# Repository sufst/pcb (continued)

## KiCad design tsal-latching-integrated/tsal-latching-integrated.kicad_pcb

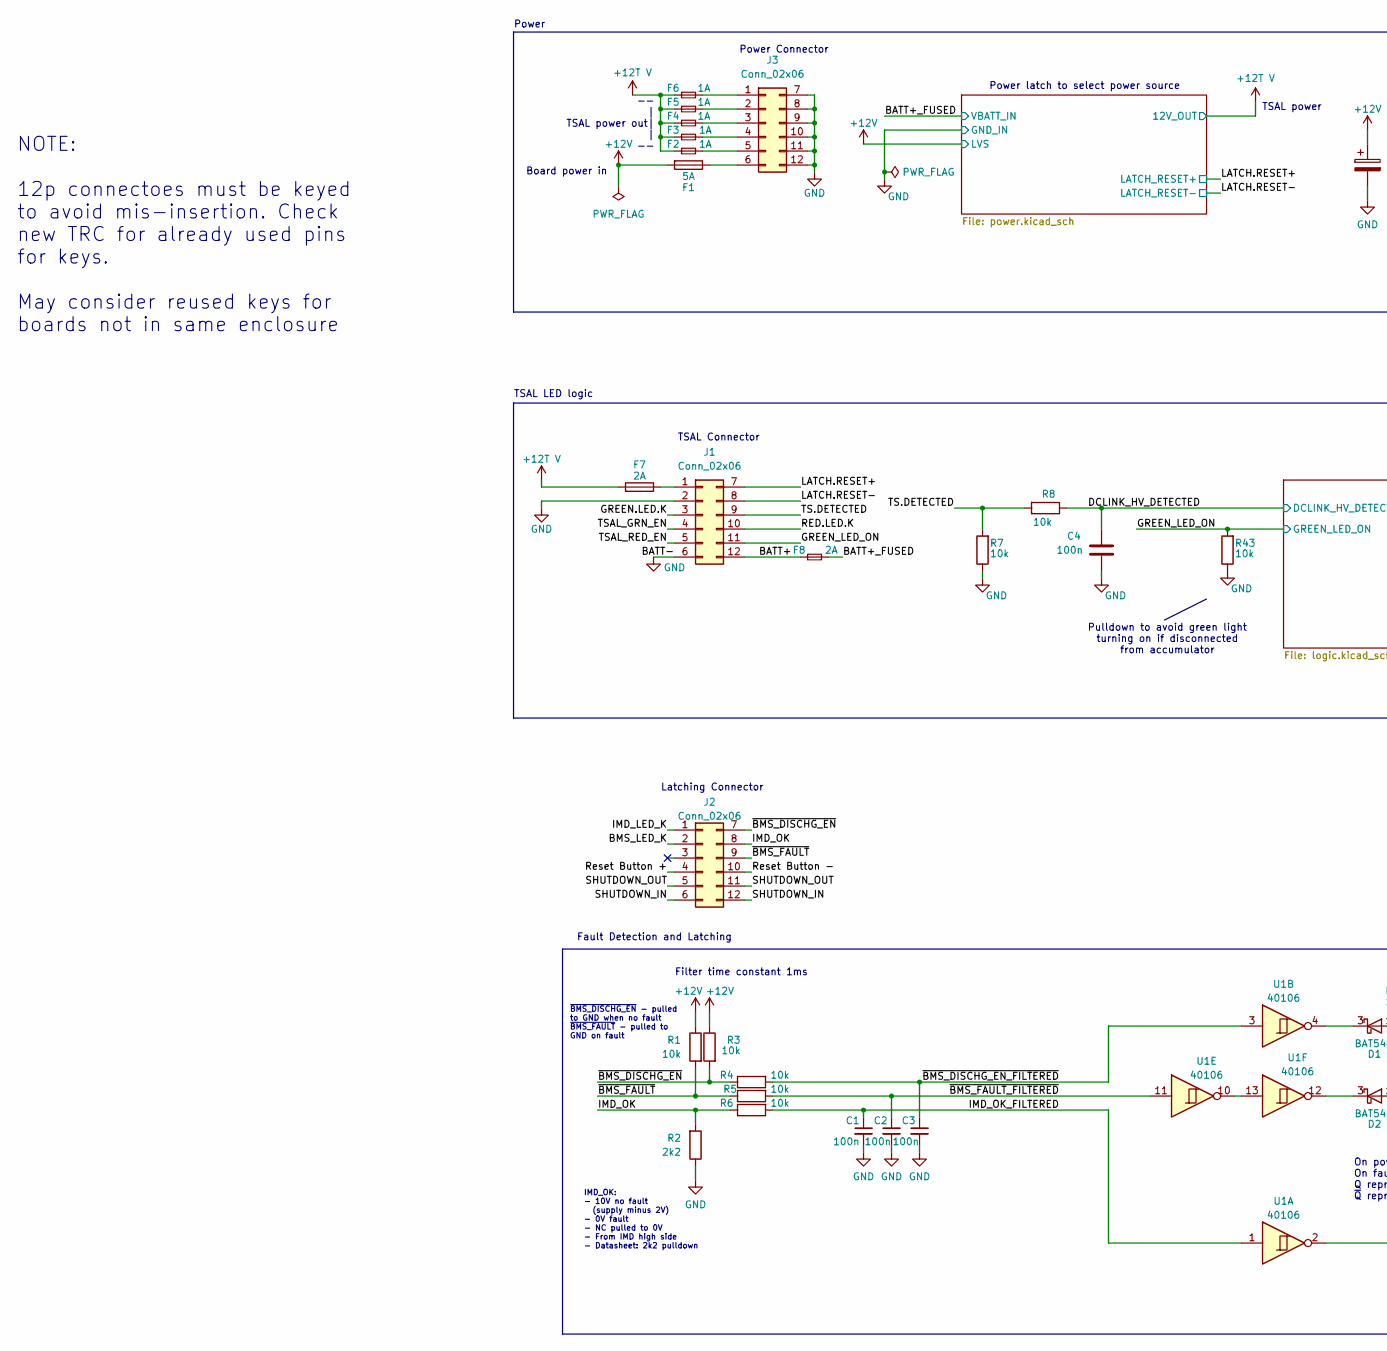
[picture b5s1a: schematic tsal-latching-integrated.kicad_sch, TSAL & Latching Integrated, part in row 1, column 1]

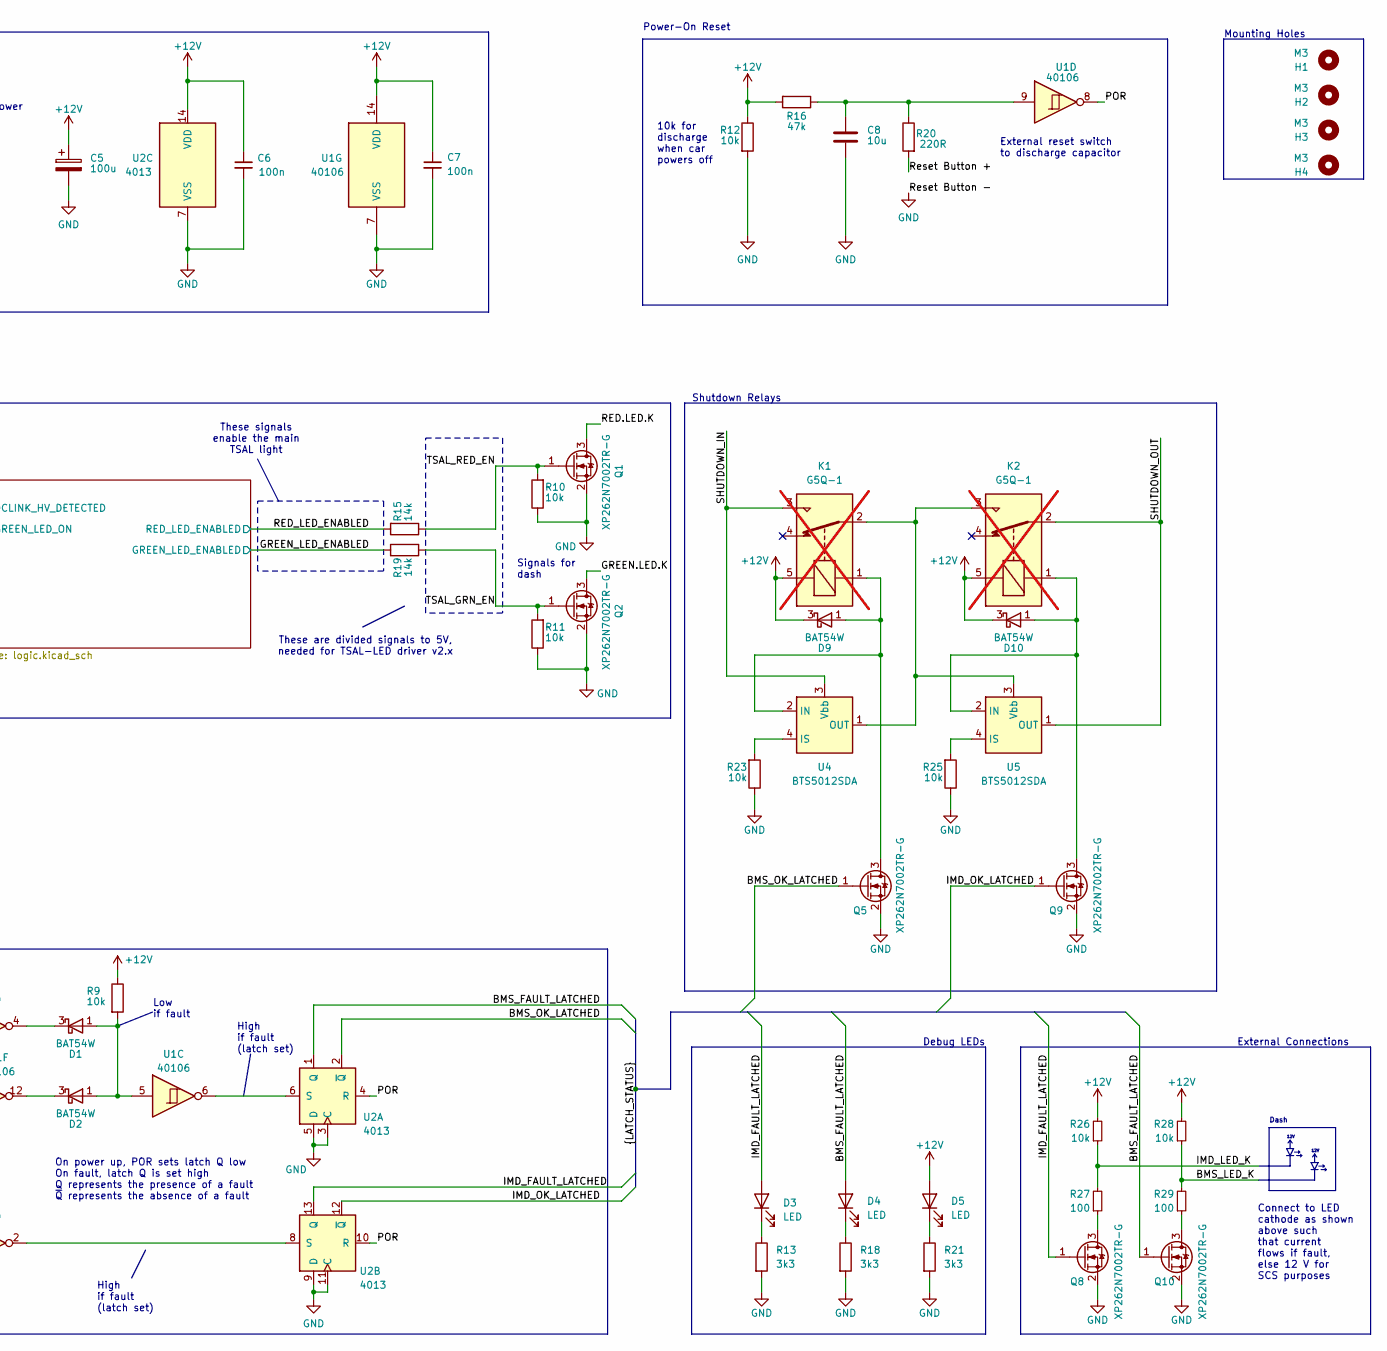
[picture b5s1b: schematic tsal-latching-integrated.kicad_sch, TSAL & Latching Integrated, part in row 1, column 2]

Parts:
C1, C2, C3, C4, C6, C7: 100n; C_0603_1608Metric; Mouser PN 187-CL10B104KB85PNL
C5: 100u; CP_Radial_D5.0mm_P2.00mm; Mouser PN 710-860010572002
C8: 10u; C_0805_2012Metric; Mouser PN 81-GRM21BR61E106KA3K
D1, D2, D9, D10: BAT54W; SOT-323_SC-70
D3, D4, D5: LED; LED_0603_1608Metric
F1: 5A; Fuse_0603_1608Metric_Pad1.05x0.95mm_HandSolder; Mouser PN 603-JB06F5001R
F2, F3, F4, F5, F6: 1A; Fuse_0603_1608Metric_Pad1.05x0.95mm_HandSolder; Mouser PN 791-FCC16102ADTP
F7, F8: 2A; Fuse_0603_1608Metric_Pad1.05x0.95mm_HandSolder; Mouser PN 791-FCC16202ADTP
H1, H2, H3, H4: M3; MountingHole_3.2mm_M3
J1, J2, J3: Conn_02x06; Molex_Micro-Fit_3.0_43045-1200_2x06_P3.00mm_Horizontal
K1, K2: G5Q-1; Relay_SPDT_Omron-G5Q-1; Mouser PN 653-G5Q-1A-EUDC12; not fitted
Q1, Q2, Q5, Q8, Q9, Q10: XP262N7002TR-G; SOT-23; Mouser PN 865-XP262N7002TR-G
R1, R3, R4, R5, R6, R7, R8, R9, R10, R11, R12, R23, R25, R26, R28, R43: 10k; R_0603_1608Metric; Mouser PN 603-RT0603FRE1310KL
R2: 2k2; R_0603_1608Metric; Mouser PN 603-RT0603FRE072K2L
R13, R18, R21: 3k3; R_0603_1608Metric; Mouser PN 594-MCT06030C3301FP5
R15, R19: 14k; R_0603_1608Metric; Mouser PN 603-RT0603FRE0714KL
R16: 47k; R_0603_1608Metric; Mouser PN 603-RT0603FRE1347KL
R20: 220R; R_0603_1608Metric; Mouser PN 603-RT0603FRE07220RL
R27, R29: 100; R_0603_1608Metric; Mouser PN 603-RT0603FRE07100RL
U1: 40106; SOIC-14_3.9x8.7mm_P1.27mm; Mouser PN 595-CD40106BM
U2: 4013; SOIC-14_3.9x8.7mm_P1.27mm
U4, U5: BTS5012SDA; TO-252-4; Mouser PN 726-BTS5012SDA

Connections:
+12T V: F2.1, F3.1, F4.1, F5.1, F6.1, F7.2; also elsewhere on the board
+12V: C5.1, C6.1, C7.1, D5.2 (A), D9.3 (K), D10.3 (K), F1.2, K1.5, K2.5, R1.1, R3.1, R9.1, R12.1, R16.2, R26.2, R28.2, U1.14 (VDD), U2.14 (VDD); also elsewhere on the board
/BATT+: F8.1, J1.12
/BATT+_FUSED: F8.2; also elsewhere on the board
/BMS_FAULT_LATCHED: D4.2 (A), Q10.1 (G), U2.1 (Q)
/BMS_LED_K: J2.2, R28.1, R29.2
/BMS_OK_LATCHED: Q5.1 (G), U2.2 (~Q)
/DCLINK_HV_DETECTED: C4.1, R8.1; also elsewhere on the board
/GREEN.LED.K: J1.3, Q2.3 (D)
/GREEN_LED_ENABLED: R19.2; also elsewhere on the board
/GREEN_LED_ON: J1.11, R43.2; also elsewhere on the board
/IMD_FAULT_LATCHED: D3.2 (A), Q8.1 (G), U2.13 (Q)
/IMD_LED_K: J2.1, R26.1, R27.2
/IMD_OK: J2.8, R2.2, R6.1
/IMD_OK_FILTERED: C1.1, R6.2, U1.1
/IMD_OK_LATCHED: Q9.1 (G), U2.12 (~Q)
/LATCH.RESET+: J1.7; also elsewhere on the board
/LATCH.RESET-: J1.8; also elsewhere on the board
/POR: U1.8, U2.4 (R), U2.10 (R)
/RED.LED.K: J1.10, Q1.3 (D)
/RED_LED_ENABLED: R15.2; also elsewhere on the board
/Reset Button +: J2.4, R20.2
/SHUTDOWN_IN: J2.6, J2.12, K1.3, U4.3 (Vbb)
/SHUTDOWN_OUT: J2.5, J2.11, K2.2, U5.1 (OUT), U5.5 (OUT)
/TS.DETECTED: J1.9, R7.2, R8.2
/TSAL_GRN_EN: J1.4, Q2.1 (G), R11.2, R19.1
/TSAL_RED_EN: J1.5, Q1.1 (G), R10.2, R15.1
/~BMS_DISCHG_EN_FILTERED: C3.1, R4.2, U1.3
/~BMS_DISCHG_EN: J2.7, R3.2, R4.1
/~BMS_FAULT_FILTERED: C2.1, R5.2, U1.11
/~BMS_FAULT: J2.9, R1.2, R5.1
GND: C1.2, C2.2, C3.2, C4.2, C5.2, C6.2, C7.2, C8.2, J1.2, J1.6, J2.10, J3.7, J3.8, J3.9, J3.10, J3.11, J3.12, Q1.2 (S), Q2.2 (S), Q5.2 (S), Q8.2 (S), Q9.2 (S), Q10.2 (S), R2.1, R7.1, R10.1, R11.1, R12.2, R13.2, R18.2, R21.2, R23.1, R25.1, R43.1, U1.7 (VSS), U2.3 (C), U2.5 (D), U2.7 (VSS), U2.9 (D), U2.11 (C); also elsewhere on the board
unnamed: C8.1, R16.1, R20.1, U1.9
unnamed: D1.1 (A), D2.1 (A), R9.2, U1.5
unnamed: D1.3 (K), U1.4
unnamed: D2.3 (K), U1.12
unnamed: D3.1 (K), R13.1
unnamed: D4.1 (K), R18.1
unnamed: D5.1 (K), R21.1
unnamed: D9.1 (A), K1.1, Q5.3 (D), U4.2 (IN)
unnamed: D10.1 (A), K2.1, Q9.3 (D), U5.2 (IN)
unnamed: F7.1, J1.1
unnamed: F6.2, J3.1
unnamed: F5.2, J3.2
unnamed: F4.2, J3.3
unnamed: F3.2, J3.4
unnamed: F2.2, J3.5
unnamed: F1.1, J3.6
unnamed: Q8.3 (D), R27.1
unnamed: Q10.3 (D), R29.1
unnamed: U1.10, U1.13
unnamed: U1.6, U2.6 (S)
unnamed: U1.2, U2.8 (S)
unnamed: R23.2, U4.4 (IS)
unnamed: R25.2, U5.4 (IS)
unnamed: K1.2, K2.3, U4.1 (OUT), U4.5 (OUT), U5.3 (Vbb)

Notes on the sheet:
Power-On Reset
These are divided signals to 5V, needed for TSAL-LED driver v2.x
IMD_OK: - 10V no fault (supply minus 2V) - 0V fault - NC pulled to 0V - From IMD high side - Datasheet: 2k2 pulldown
Low if fault
Board power in
TSAL Connector
High if fault (latch set)
Filter time constant 1ms
Debug LEDs
Dash
TSAL LED logic
TSAL power
12V
NOTE: 12p connectoes must be keyed to avoid mis-insertion. Check new TRC for already used pins for keys. May consider reused keys for boards not in same enclosure
Latching Connector
Shutdown Relays
Signals for dash
Power latch to select power source
-- | TSAL power out| | --
Connect to LED cathode as shown above such that current flows if fault, else 12 V for SCS purposes
Pulldown to avoid green light turning on if disconnected from accumulator
External reset switch to discharge capacitor
Power
These signals enable the main TSAL light
10k for discharge when car powers off
~{BMS_DISCHG_EN} - pulled to GND when no fault ~{BMS_FAULT} - pulled to GND on fault
High if fault (latch set)
On power up, POR sets latch Q low On fault, latch Q is set high Q represents the presence of a fault ~{Q} represents the absence of a fault
Fault Detection and Latching
External Connections
Power Connector
Mounting Holes

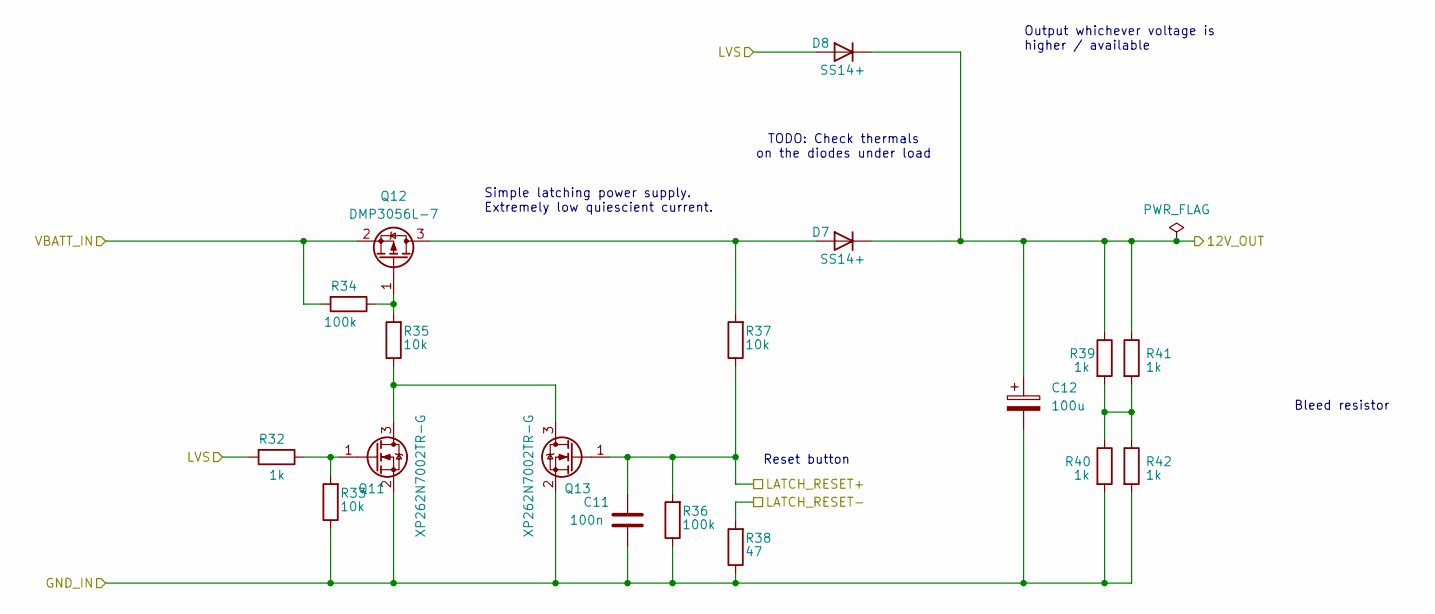
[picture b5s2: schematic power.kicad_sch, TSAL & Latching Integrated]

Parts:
C11: 100n; C_0603_1608Metric; Mouser PN 187-CL10B104KB85PNL
C12: 100u; CP_Radial_D6.3mm_P2.50mm
D7, D8: SS14+; D_SMA
Q11, Q13: XP262N7002TR-G; SOT-23; Mouser PN 865-XP262N7002TR-G
Q12: DMP3056L-7; SOT-23; Mouser PN 621-DMP3056L-7
R32, R39, R40, R41, R42: 1k; R_0603_1608Metric; Mouser PN 708-RNCP0603FTD1K00
R33, R35, R37: 10k; R_0603_1608Metric; Mouser PN 603-RT0603FRE1310KL
R34, R36: 100k; R_0603_1608Metric; Mouser PN 603-RT0603FRE10100KL
R38: 47; R_0603_1608Metric; Mouser PN 603-RT0603FRE0747RL

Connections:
+12T V: C12.1, D7.1 (K), D8.1 (K), R39.1, R41.1; also elsewhere on the board
+12V: D8.2 (A), R32.2; also elsewhere on the board
/BATT+_FUSED: Q12.2 (S), R34.2; also elsewhere on the board
/LATCH.RESET+: C11.1, Q13.1 (G), R36.2, R37.1; also elsewhere on the board
/LATCH.RESET-: R38.2; also elsewhere on the board
GND: C11.2, C12.2, Q11.2 (S), Q13.2 (S), R33.1, R36.1, R38.1, R40.2, R42.2; also elsewhere on the board
unnamed: D7.2 (A), Q12.3 (D), R37.2
unnamed: Q11.3 (D), Q13.3 (D), R35.1
unnamed: Q11.1 (G), R32.1, R33.2
unnamed: Q12.1 (G), R34.1, R35.2
unnamed: R39.2, R40.1, R41.2, R42.1

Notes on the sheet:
Bleed resistor
Simple latching power supply. Extremely low quiescient current.
TODO: Check thermals on the diodes under load
Output whichever voltage is higher / available
Reset button

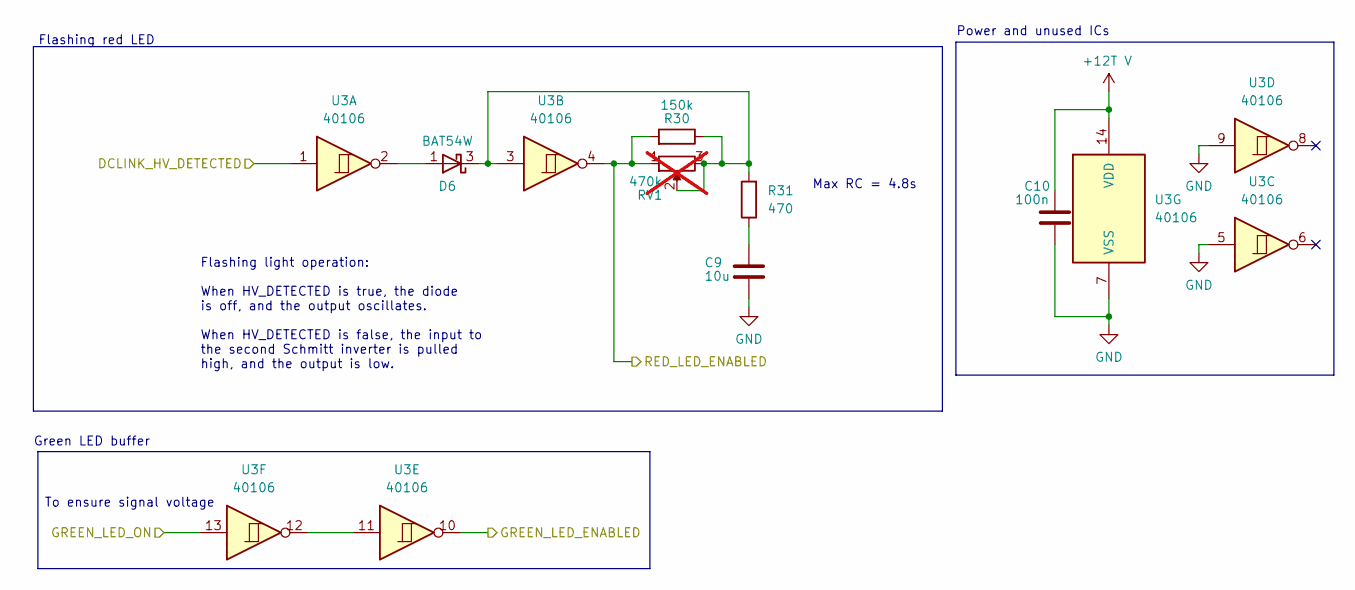
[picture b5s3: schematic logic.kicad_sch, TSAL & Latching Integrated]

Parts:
C9: 10u; C_0805_2012Metric; Mouser PN 81-GRM21BR61E106KA3K
C10: 100n; C_0603_1608Metric; Mouser PN 187-CL10B104KB85PNL
D6: BAT54W; SOT-323_SC-70
R30: 150k; R_0603_1608Metric; Mouser PN 603-RT0603FRE13150KL
R31: 470; R_0603_1608Metric; Mouser PN 603-RT0603FRD07470RL
RV1: 470k; Potentiometer_Bourns_3296W_Vertical; not fitted
U3: 40106; SOIC-14_3.9x8.7mm_P1.27mm; Mouser PN 595-CD40106BM

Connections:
+12T V: C10.1, U3.14 (VDD); also elsewhere on the board
/DCLINK_HV_DETECTED: U3.1; also elsewhere on the board
/GREEN_LED_ENABLED: U3.10; also elsewhere on the board
/GREEN_LED_ON: U3.13; also elsewhere on the board
/RED_LED_ENABLED: R30.2, RV1.1, U3.4; also elsewhere on the board
GND: C9.2, C10.2, U3.5, U3.7 (VSS), U3.9; also elsewhere on the board
unnamed: C9.1, R31.1
unnamed: D6.1 (A), U3.2
unnamed: D6.3 (K), R30.1, R31.2, RV1.2, RV1.3, U3.3
unnamed: U3.11, U3.12

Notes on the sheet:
Power and unused ICs
Flashing red LED
Max RC = 4.8s
Flashing light operation: When HV_DETECTED is true, the diode is off, and the output oscillates. When HV_DETECTED is false, the input to the second Schmitt inverter is pulled high, and the output is low.
To ensure signal voltage
Green LED buffer

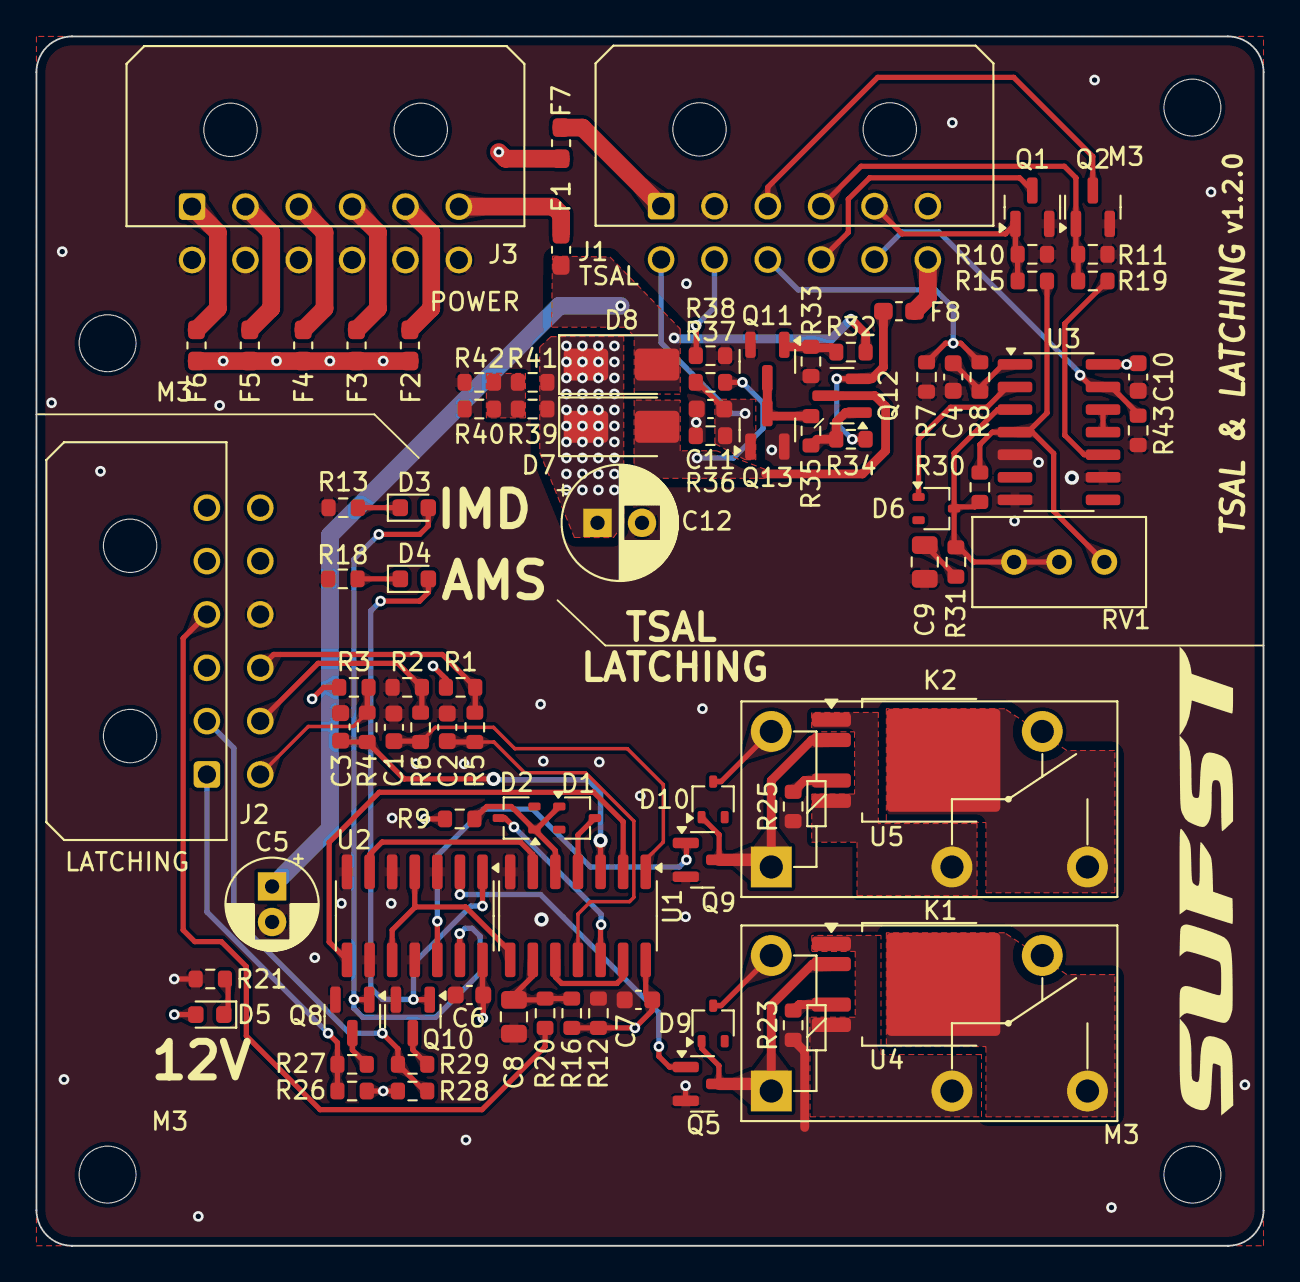
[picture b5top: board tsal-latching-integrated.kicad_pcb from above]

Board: 4 copper layers, 69.0 x 68.0 mm, 93 parts (0 on the bottom side), 65 nets.

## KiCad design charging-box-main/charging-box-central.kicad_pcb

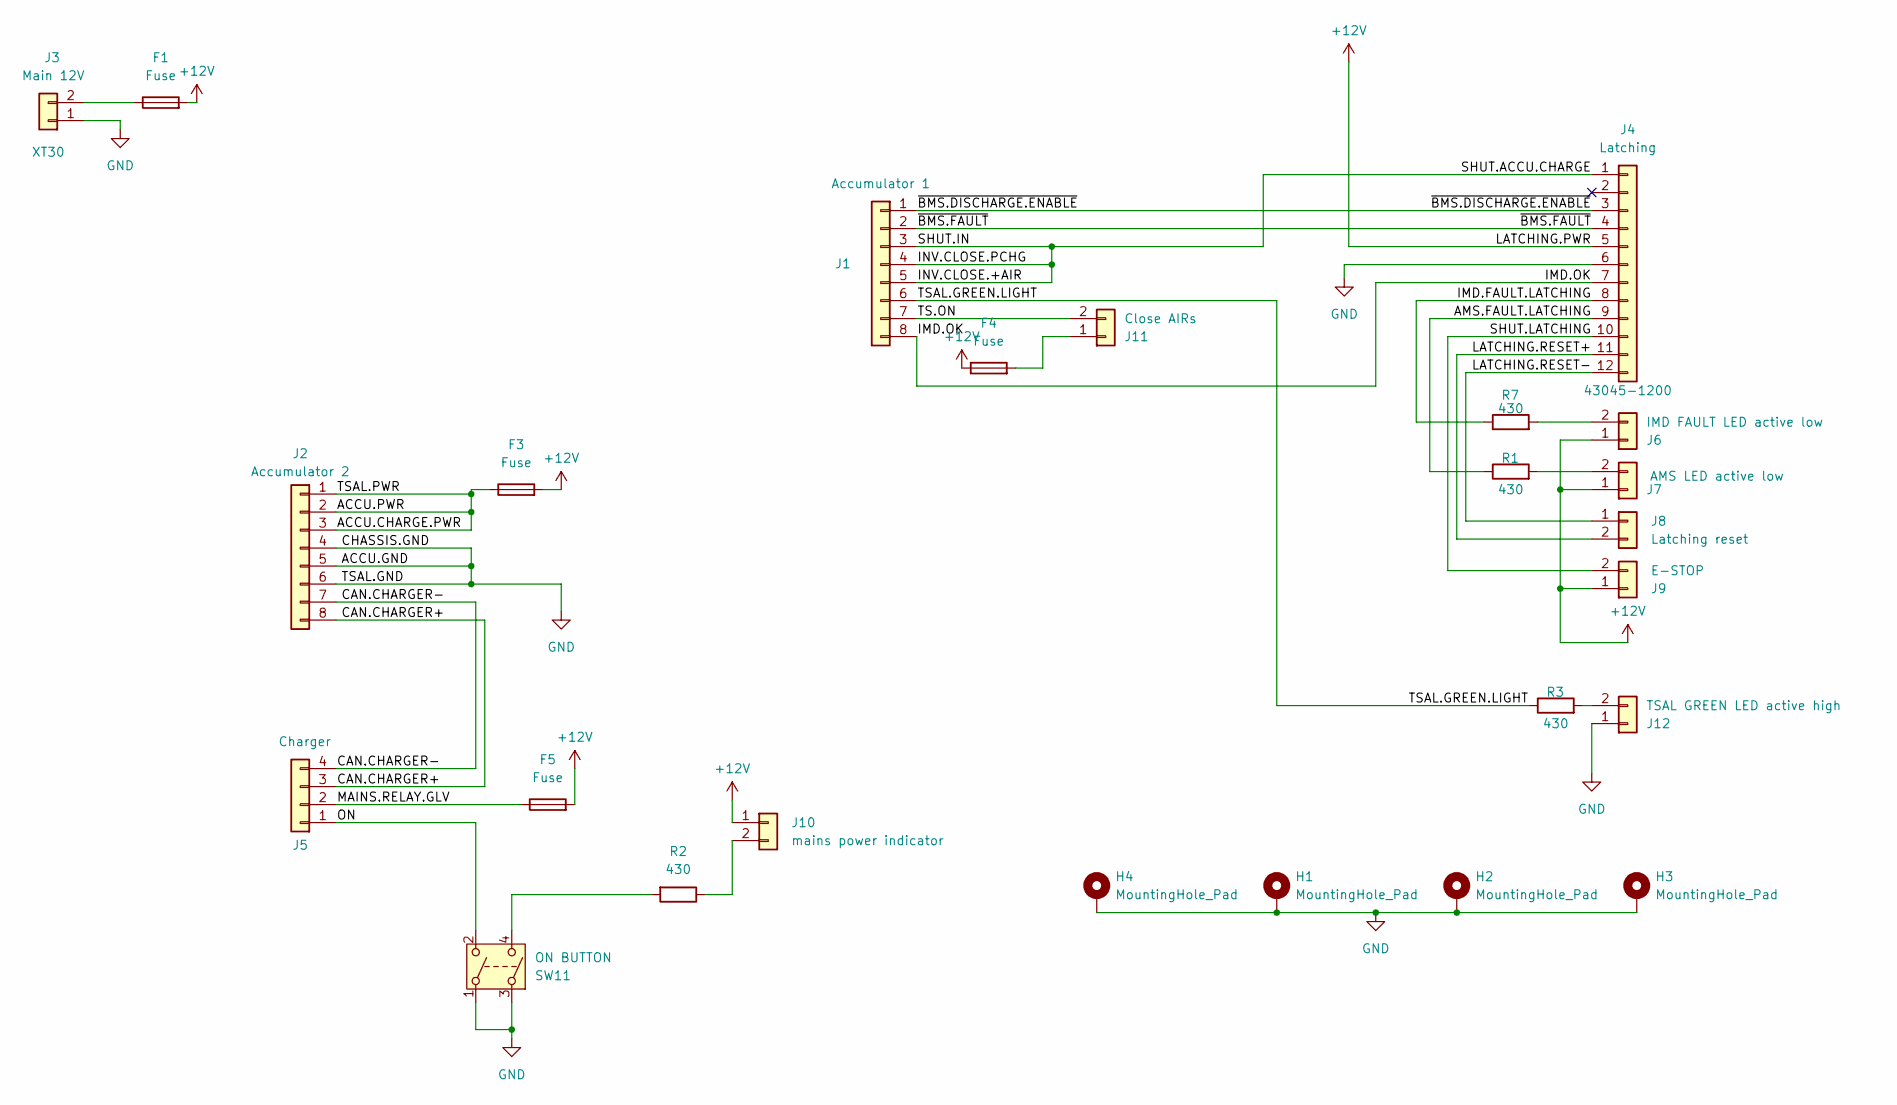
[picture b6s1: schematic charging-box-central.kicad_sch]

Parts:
F1, F3, F4, F5: Fuse; Fuse_0603_1608Metric
H1, H2, H3, H4: MountingHole_Pad; MountingHole_3.2mm_M3_DIN965_Pad_TopBottom
J1: Accumulator 1; Molex_Micro-Fit_3.0_43045-0800_2x04_P3.00mm_Horizontal
J2: Accumulator 2; Molex_Micro-Fit_3.0_43045-0800_2x04_P3.00mm_Horizontal
J3: Main 12V; AMASS_XT30PW-M_1x02_P2.50mm_Horizontal
J4: Latching; Molex_Micro-Fit_3.0_43045-1200_2x06_P3.00mm_Horizontal
J5: Charger; Molex_Micro-Fit_3.0_43045-0400_2x02_P3.00mm_Horizontal
J6: IMD FAULT LED active low; Molex_Micro-Fit_3.0_43045-0200_2x01_P3.00mm_Horizontal
J7: AMS LED active low; Molex_Micro-Fit_3.0_43045-0200_2x01_P3.00mm_Horizontal
J8: Latching reset; Molex_Micro-Fit_3.0_43045-0200_2x01_P3.00mm_Horizontal
J9: E-STOP; Molex_Micro-Fit_3.0_43045-0200_2x01_P3.00mm_Horizontal
J10: mains power indicator; Molex_Micro-Fit_3.0_43045-0200_2x01_P3.00mm_Horizontal
J11: Close AIRs; Molex_Micro-Fit_3.0_43045-0200_2x01_P3.00mm_Horizontal
J12: TSAL GREEN LED active high; Molex_Micro-Fit_3.0_43045-0200_2x01_P3.00mm_Horizontal
R1, R2, R3, R7: 430; R_0805_2012Metric_Pad1.20x1.40mm_HandSolder
SW11: ON BUTTON; Molex_Micro-Fit_3.0_43045-0400_2x02_P3.00mm_Horizontal

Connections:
+12V: F1.2, F3.2, F4.1, F5.2, J4.5, J6.1, J7.1, J9.1, J10.1; also elsewhere on the board
/ACCU.CHARGE.PWR: F3.1, J2.1, J2.2, J2.3
/AMS.FAULT.LATCHING: J4.9, R1.1
/CAN.CHARGER+: J2.8, J5.3
/CAN.CHARGER-: J2.7, J5.4
/IMD.FAULT.LATCHING: J4.8, R7.1
/IMD.OK: J1.8, J4.7
/INV.CLOSE.+AIR: J1.3, J1.4, J1.5, J4.1
/LATCHING.RESET+: J4.11, J8.2
/LATCHING.RESET-: J4.12, J8.1
/MAINS.RELAY.GLV: F5.1, J5.2
/ON: J5.1, SW11.2
/SHUT.LATCHING: J4.10, J9.2
/TS.ON: J1.7, J11.2
/~BMS.DISCHARGE.ENABLE: J1.1, J4.3
/~BMS.FAULT: J1.2, J4.4
GND: H1.1, H2.1, H3.1, H4.1, J2.4, J2.5, J2.6, J3.1, J4.6, J12.1, SW11.1, SW11.3
unnamed: F1.1, J3.2
unnamed: J6.2, R7.2
unnamed: J7.2, R1.2
unnamed: J10.2, R2.1
unnamed: F4.2, J11.1
unnamed: J12.2, R3.2
unnamed: R2.2, SW11.4

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
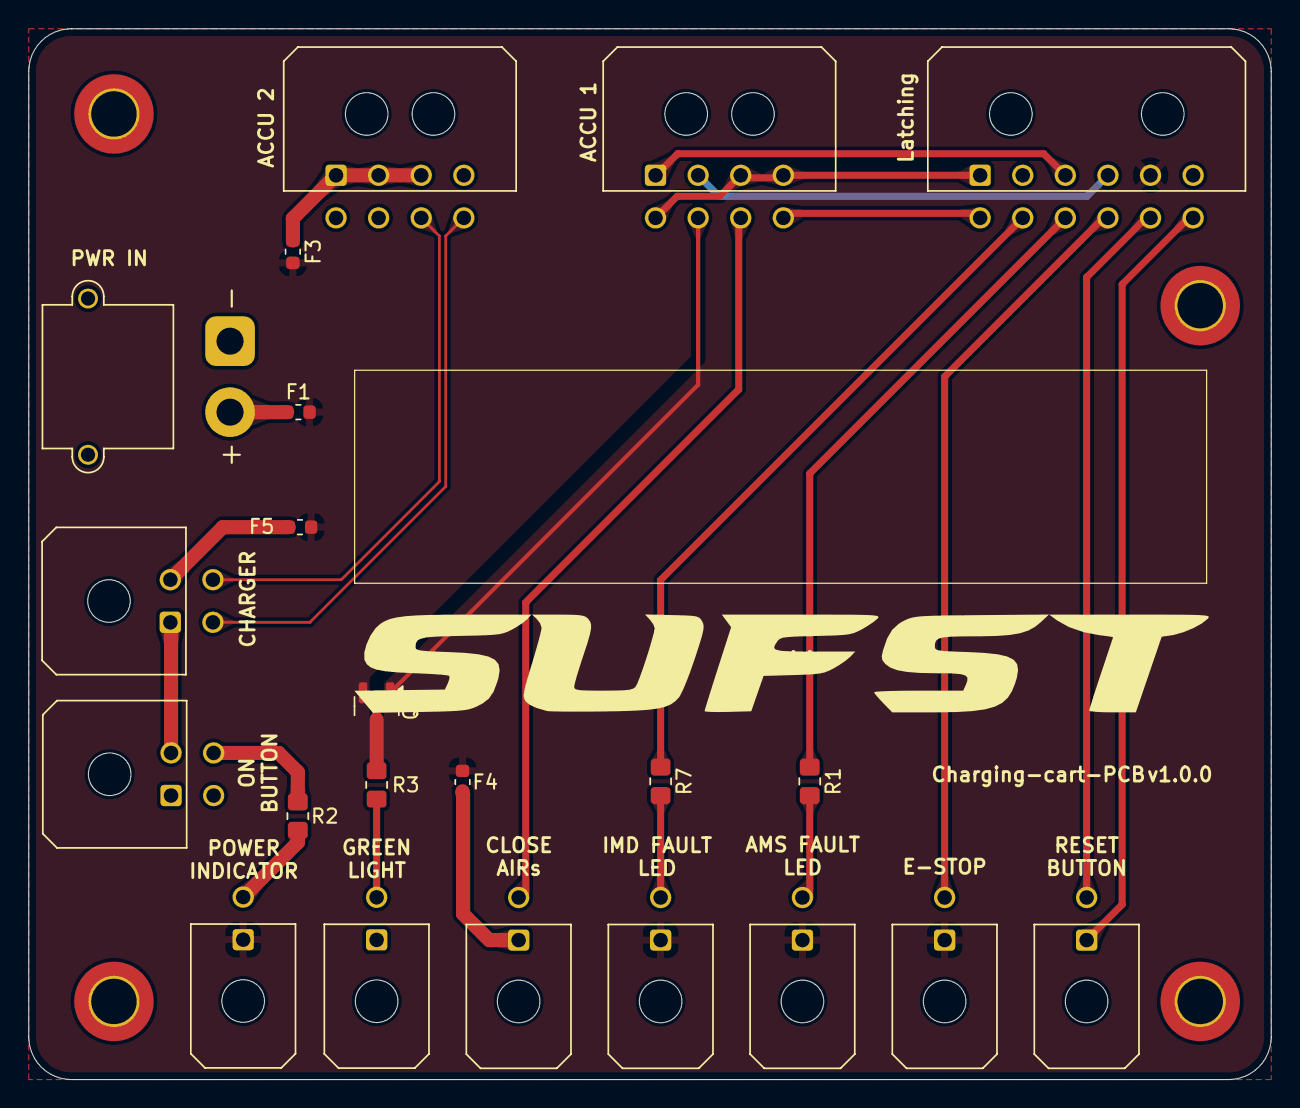
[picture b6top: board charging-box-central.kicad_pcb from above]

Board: 2 copper layers, 87.5 x 74.0 mm, 26 parts (0 on the bottom side), 26 nets.

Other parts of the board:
Q1: Q_PMOS-E_Generic_GSD; SOT-23

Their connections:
+12V: Q1.2 (S); also elsewhere on the board

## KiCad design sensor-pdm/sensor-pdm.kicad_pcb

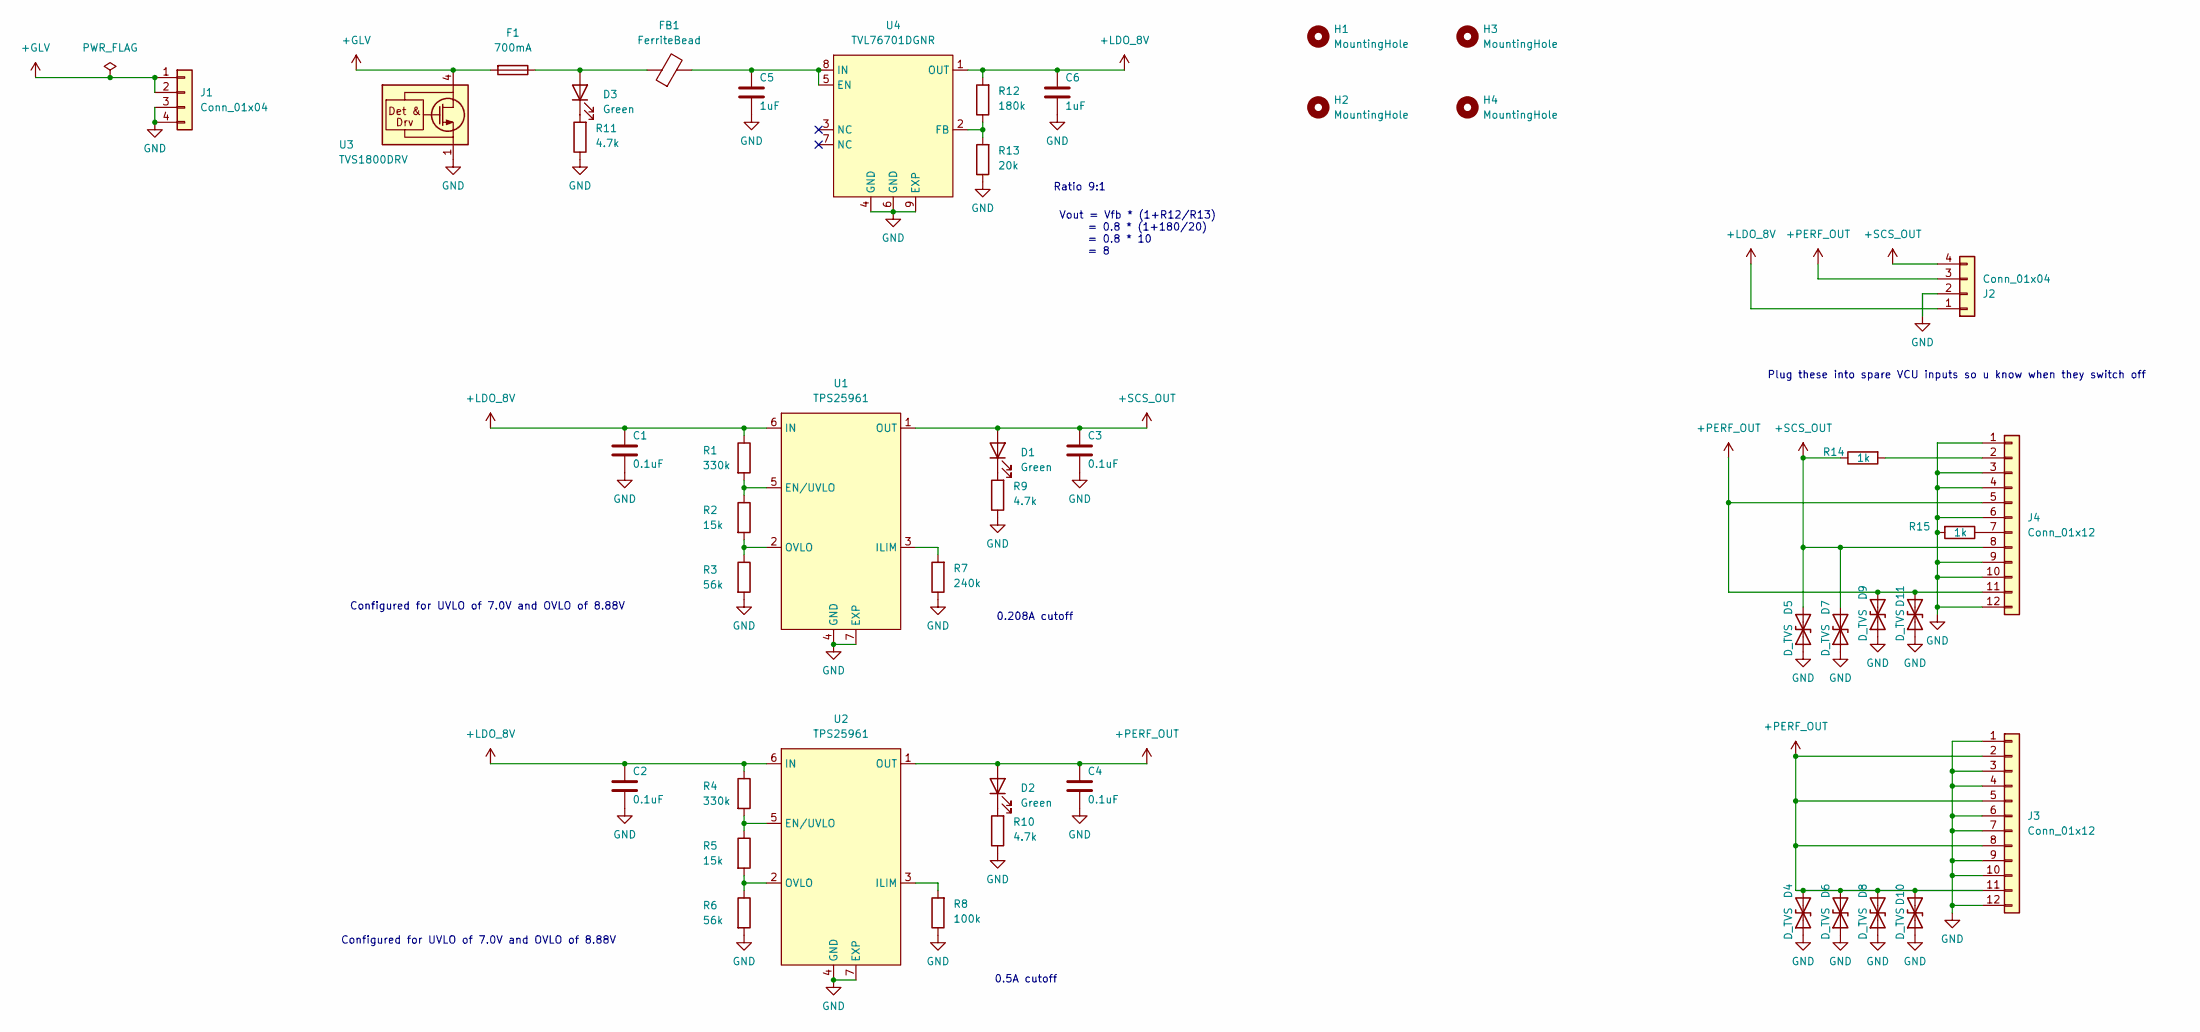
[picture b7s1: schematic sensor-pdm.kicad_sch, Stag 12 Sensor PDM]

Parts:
C1, C2, C3, C4: 0.1uF; C_0603_1608Metric_Pad1.08x0.95mm_HandSolder; Mouser Part Number 963-UMK107BJ105KA-T
C5, C6: 1uF; C_0603_1608Metric_Pad1.08x0.95mm_HandSolder; Mouser Part Number 963-UMK107BJ105KA-T
D1, D2, D3: Green; LED_0603_1608Metric_Pad1.05x0.95mm_HandSolder; Mouser Part Number 755-SML-D12P8WT86
D4, D5, D6, D7, D8, D9, D10, D11: D_TVS; D_SOD-323_wide; Mouser Order Number 595-TSD36DYFRQ1
F1: 700mA; Fuse_0603_1608Metric_Pad1.05x0.95mm_HandSolder; Mouser Part Number 603-JB06F5001R
FB1: FerriteBead; L_0805_2012Metric_Pad1.05x1.20mm_HandSolder
H1, H2, H3, H4: MountingHole; MountingHole_3.2mm_M3_DIN965
J1, J2: Conn_01x04; Molex_Micro-Fit_3.0_43045-0400_2x02_P3.00mm_Horizontal
J3, J4: Conn_01x12; Molex_Micro-Fit_3.0_43045-1200_2x06_P3.00mm_Horizontal
R1, R4: 330k; R_0603_1608Metric_Pad0.98x0.95mm_HandSolder; Mouser Part Number 708-RNCP0603FTD10K0
R2, R5: 15k; R_0603_1608Metric_Pad0.98x0.95mm_HandSolder; Mouser Part Number 708-RNCP0603FTD10K0
R3, R6: 56k; R_0603_1608Metric_Pad0.98x0.95mm_HandSolder; Mouser Part Number 708-RNCP0603FTD10K0
R7: 240k; R_0603_1608Metric_Pad0.98x0.95mm_HandSolder; Mouser Part Number 708-RNCP0603FTD10K0
R8: 100k; R_0603_1608Metric_Pad0.98x0.95mm_HandSolder; Mouser Part Number 708-RNCP0603FTD10K0
R9, R10, R11: 4.7k; R_0603_1608Metric_Pad0.98x0.95mm_HandSolder; Mouser Part Number 708-RNCP0603FTD10K0
R12: 180k; R_0603_1608Metric_Pad0.98x0.95mm_HandSolder; Mouser Part Number 708-RNCP0603FTD10K0
R13: 20k; R_0603_1608Metric_Pad0.98x0.95mm_HandSolder; Mouser Part Number 708-RNCP0603FTD10K0
R14, R15: 1k; R_0603_1608Metric_Pad0.98x0.95mm_HandSolder; Mouser Part Number 708-RNCP0603FTD10K0
U1, U2: TPS25961; TPS73733DRVR
U3: TVS1800DRV; WSON-6-1EP_2x2mm_P0.65mm_EP1x1.6mm
U4: TVL76701DGNR; HVSSOP-8-1EP_3x3mm_P0.65mm_EP1.57x1.89mm

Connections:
+GLV: F1.2, J1.1, J1.2, U3.4 (IN), U3.5 (IN), U3.6 (IN)
+LDO_8V: C1.2, C2.2, C6.2, J2.1, R1.1, R4.1, R12.2, U1.6 (IN), U2.6 (IN), U4.1 (OUT)
+PERF_OUT: C4.2, D2.2 (A), D4.2 (A2), D6.2 (A2), D8.2 (A2), D9.2 (A2), D10.2 (A2), D11.2 (A2), J2.3, J3.2, J3.5, J3.8, J3.11, J4.5, J4.11, U2.1 (OUT)
+SCS_OUT: C3.2, D1.2 (A), D5.2 (A2), D7.2 (A2), J2.4, J4.8, R14.1, U1.1 (OUT)
GND: C1.1, C2.1, C3.1, C4.1, C5.1, C6.1, D4.1 (A1), D5.1 (A1), D6.1 (A1), D7.1 (A1), D8.1 (A1), D9.1 (A1), D10.1 (A1), D11.1 (A1), J1.3, J1.4, J2.2, J3.1, J3.3, J3.4, J3.6, J3.7, J3.9, J3.10, J3.12, J4.1, J4.3, J4.4, J4.6, J4.9, J4.10, J4.12, R3.2, R6.2, R7.1, R8.1, R9.1, R10.1, R11.1, R13.1, R15.2, U1.4 (GND), U1.7 (EXP), U2.4 (GND), U2.7 (EXP), U3.1 (GND), U3.2 (GND), U3.3 (GND), U3.7 (GND), U4.4 (GND), U4.6 (GND), U4.9 (EXP)
unnamed: D1.1 (K), R9.2
unnamed: D2.1 (K), R10.2
unnamed: D3.2 (A), F1.1, FB1.1
unnamed: D3.1 (K), R11.2
unnamed: J4.2, R14.2
unnamed: J4.7, R15.1
unnamed: R1.2, R2.1, U1.5 (EN/UVLO)
unnamed: R7.2, U1.3 (ILIM)
unnamed: R2.2, R3.1, U1.2 (OVLO)
unnamed: R4.2, R5.1, U2.5 (EN/UVLO)
unnamed: R8.2, U2.3 (ILIM)
unnamed: R5.2, R6.1, U2.2 (OVLO)
unnamed: C5.2, FB1.2, U4.5 (EN), U4.8 (IN)
unnamed: R12.1, R13.2, U4.2 (FB)

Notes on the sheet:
Vout = Vfb * (1+R12/R13) = 0.8 * (1+180/20) = 0.8 * 10 = 8
0.5A cutoff
Plug these into spare VCU inputs so u know when they switch off
Configured for UVLO of 7.0V and OVLO of 8.88V
Ratio 9:1
0.208A cutoff

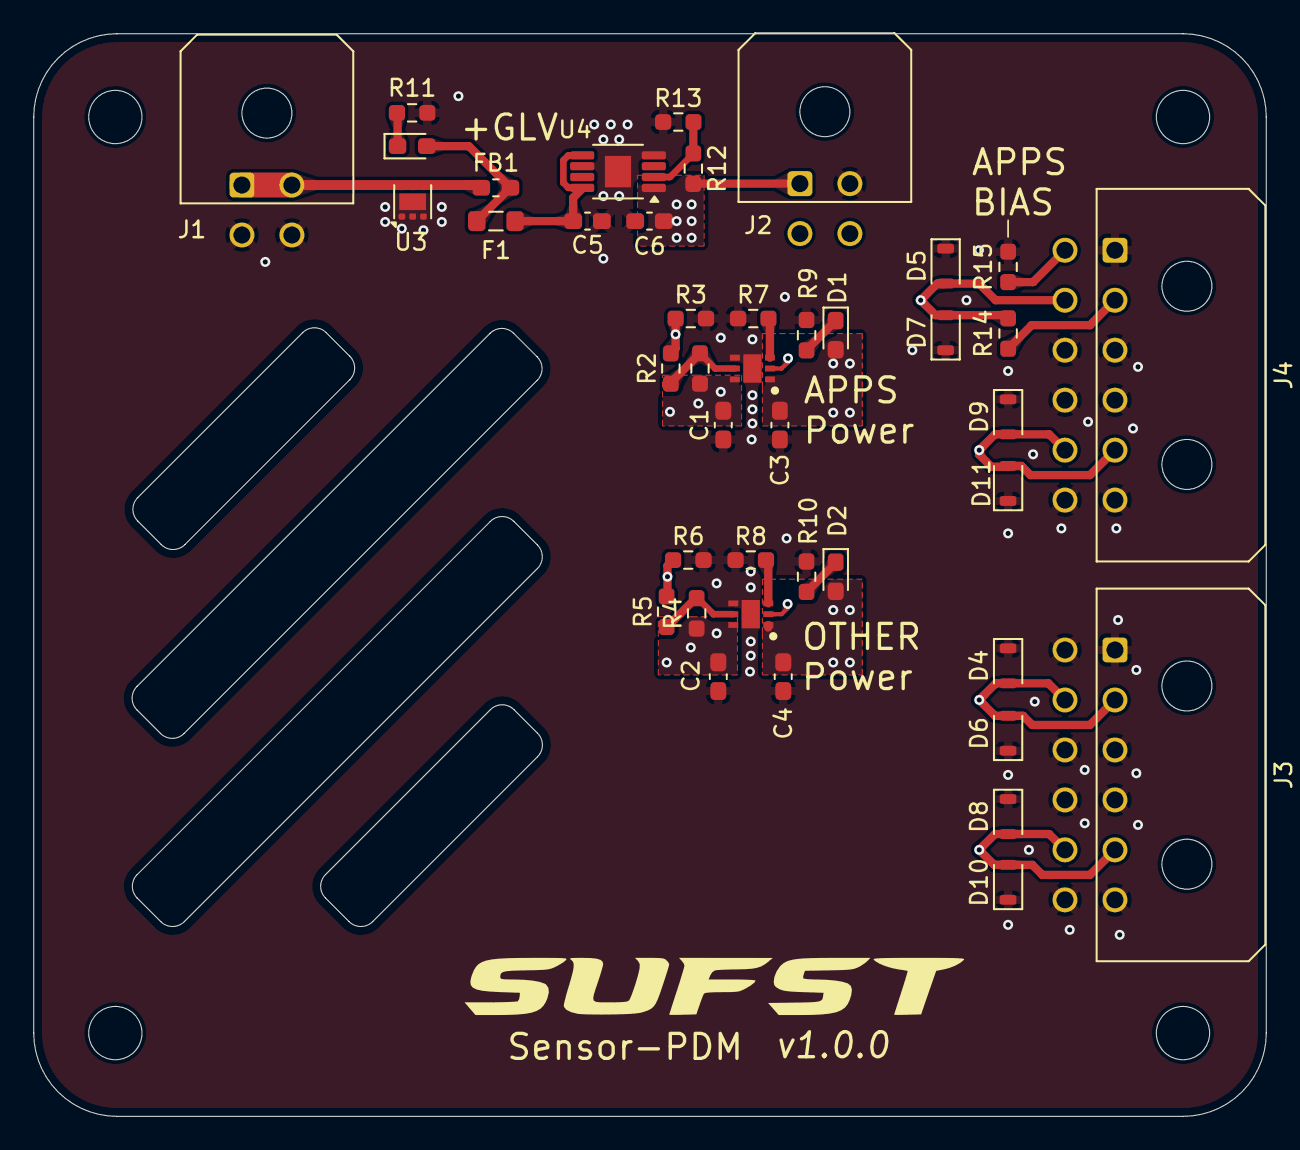
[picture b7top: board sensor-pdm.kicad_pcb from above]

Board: 4 copper layers, 74.0 x 65.0 mm, 46 parts (0 on the bottom side), 19 nets.
